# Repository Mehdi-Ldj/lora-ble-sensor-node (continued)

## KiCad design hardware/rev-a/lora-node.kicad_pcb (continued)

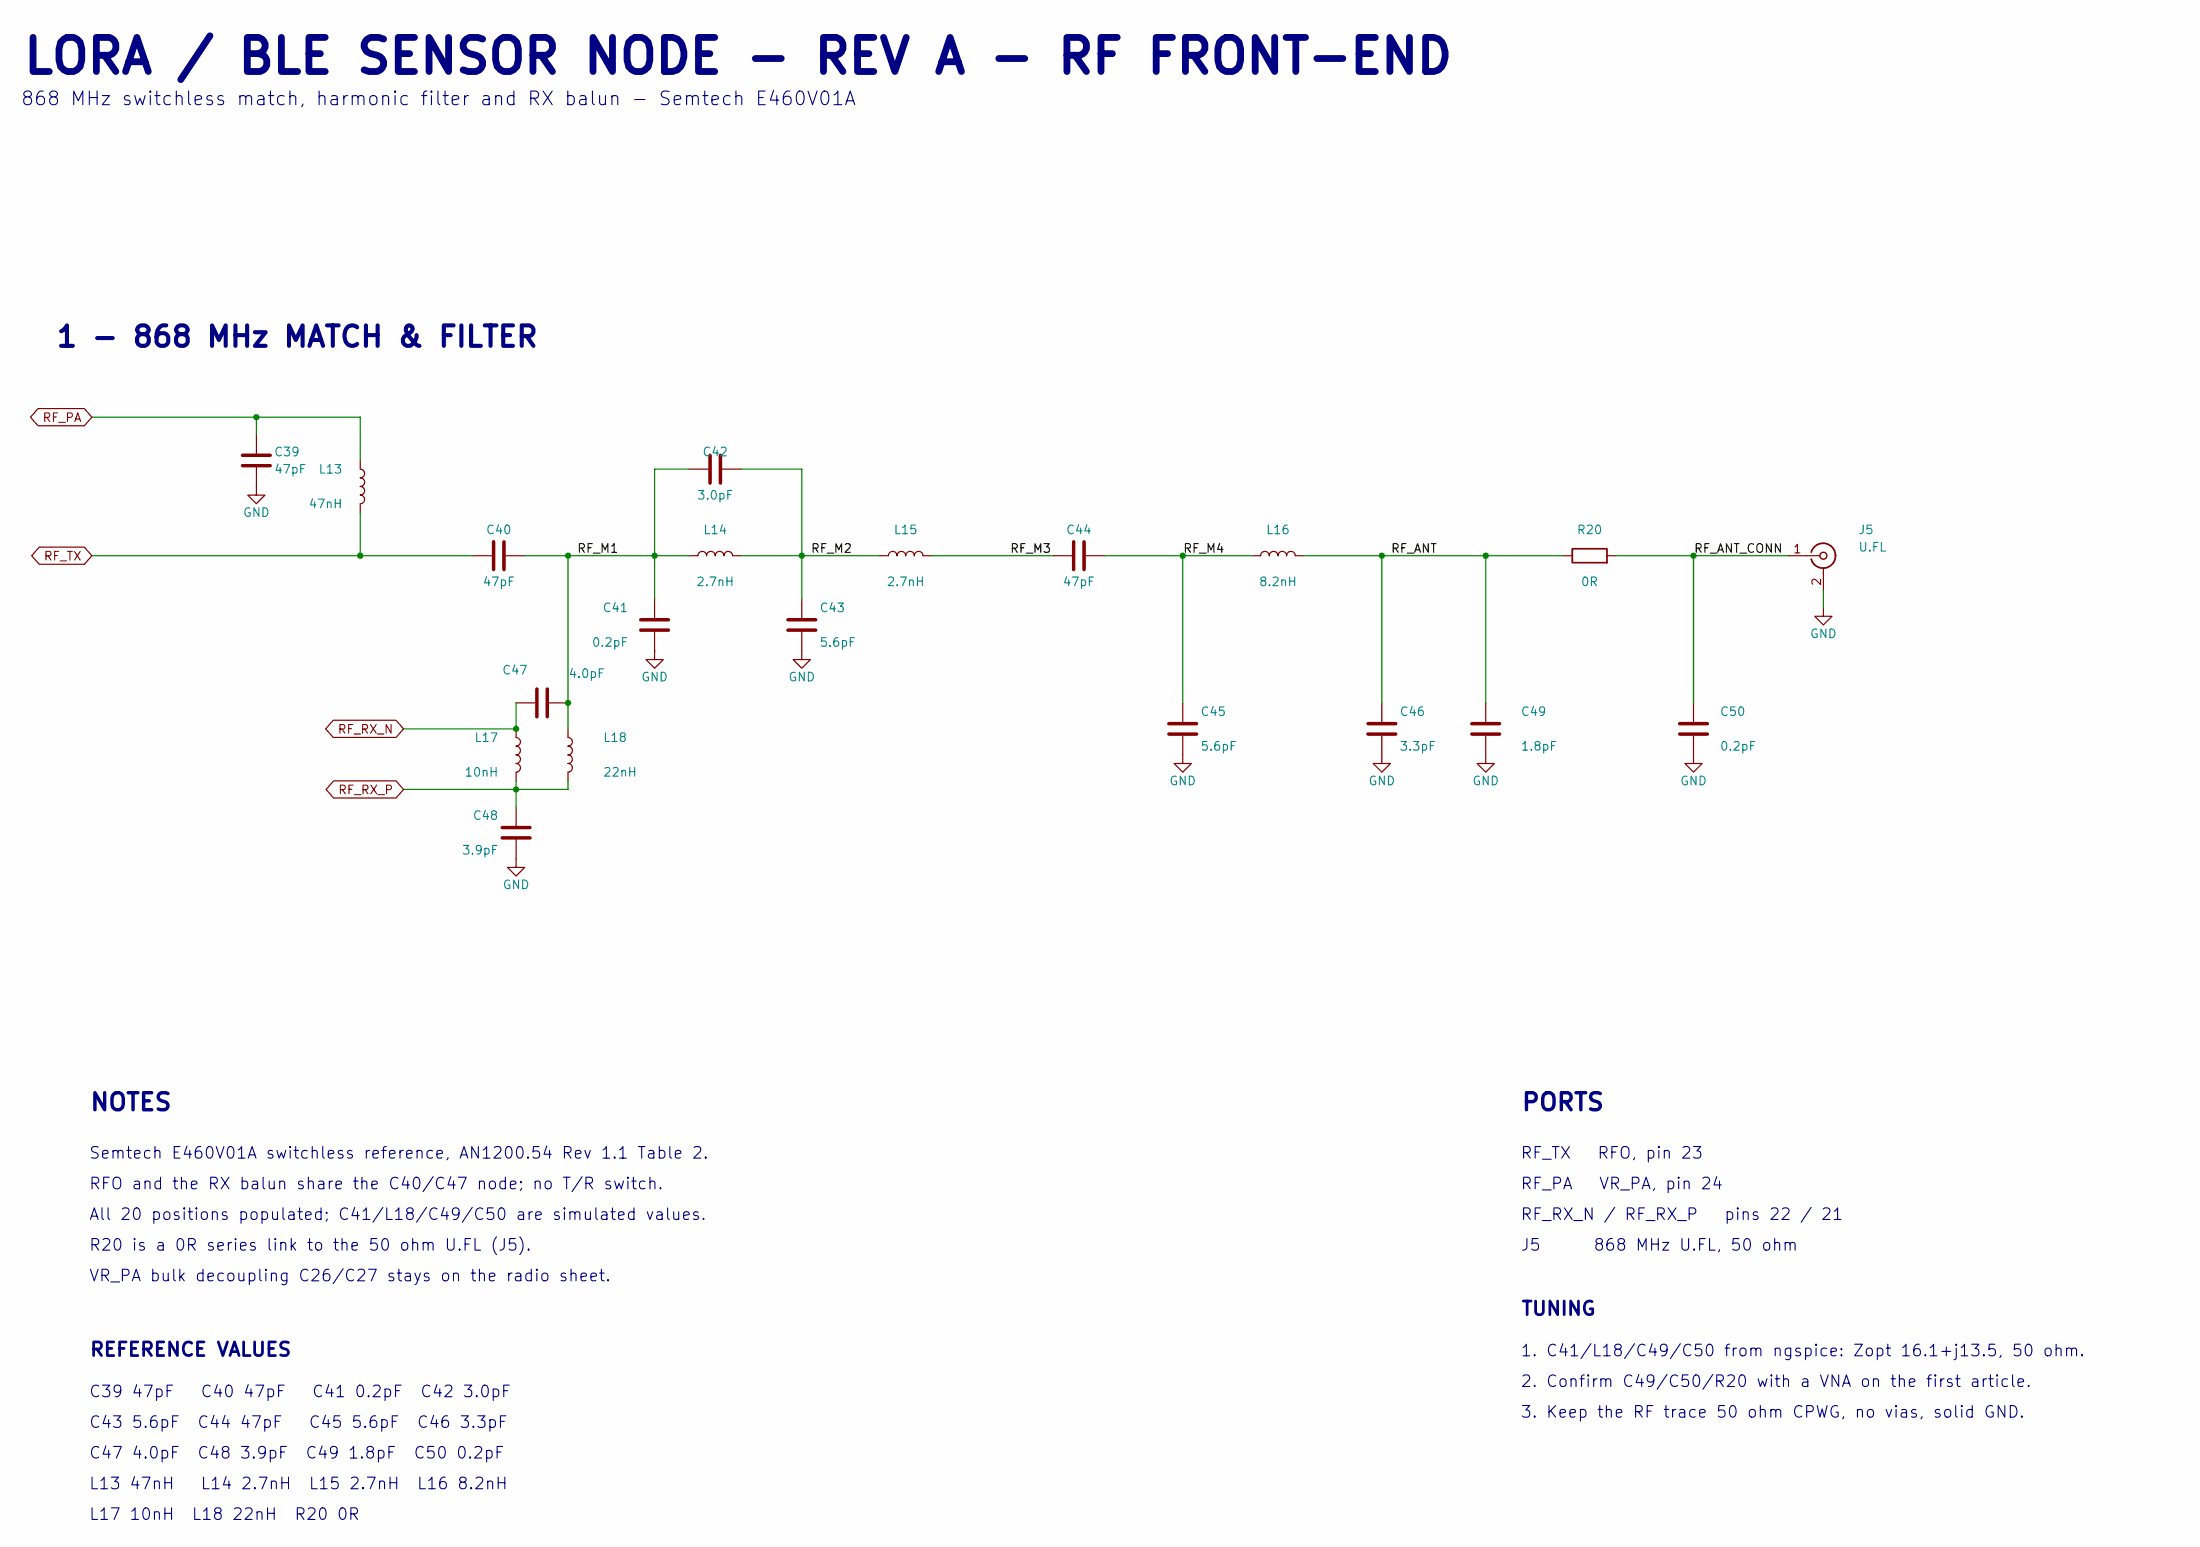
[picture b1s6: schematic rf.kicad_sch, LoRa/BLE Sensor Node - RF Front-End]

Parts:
C39, C40, C44: 47pF; C_0402_1005Metric; MPN CC0402JRNPO9BN470; LCSC C60137
C41, C50: 0.2pF; C_0402_1005Metric; MPN CQ0402BRNPO9BNR20; LCSC C1855077
C42: 3.0pF; C_0402_1005Metric; MPN CC0402BRNPO9BN3R0; LCSC C327228
C43, C45: 5.6pF; C_0402_1005Metric; MPN CC0402BRNPO9BN5R6; LCSC C505468
C46: 3.3pF; C_0402_1005Metric; MPN CC0402BRNPO9BN3R3; LCSC C327287
C47: 4.0pF; C_0402_1005Metric; MPN CC0402BRNPO9BN4R0; LCSC C541337
C48: 3.9pF; C_0402_1005Metric; MPN CC0402BRNPO9BN3R9; LCSC C505474
C49: 1.8pF; C_0402_1005Metric; MPN CC0402BRNPO9BN1R8; LCSC C327209
J5: U.FL; U.FL_Hirose_U.FL-R-SMT-1_Vertical; MPN U.FL-R-SMT-1(80); LCSC C88374
L13: 47nH; L_0402_1005Metric; MPN LQW15AN47NG00D; LCSC C22334
L14, L15: 2.7nH; L_0402_1005Metric; MPN LQW15AN2N7C00D; LCSC C98058
L16: 8.2nH; L_0402_1005Metric; MPN LQW15AN8N2G00D; LCSC C84404
L17: 10nH; L_0402_1005Metric; MPN LQW15AN10NG00D; LCSC C90642
L18: 22nH; L_0402_1005Metric; MPN LQW15AN22NG00D; LCSC C86129
R20: 0R; R_0402_1005Metric; MPN 0402WGF0000TCE; LCSC C17168

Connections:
/RF/RF_ANT: C46.1, C49.1, L16.2, R20.1
/RF/RF_ANT_CONN: C50.1, J5.1 (In), R20.2
/RF/RF_M1: C40.2, C41.1, C42.1, C47.1, L14.1, L18.1
/RF/RF_M2: C42.2, C43.1, L14.2, L15.1
/RF/RF_M3: C44.1, L15.2
/RF/RF_M4: C44.2, C45.1, L16.1
GND: C39.2, C41.2, C43.2, C45.2, C46.2, C48.2, C49.2, C50.2, J5.2 (Ext); also elsewhere on the board
RF_PA: C39.1, L13.1; also elsewhere on the board
RF_RX_N: C47.2, L17.1; also elsewhere on the board
RF_RX_P: C48.1, L17.2, L18.2; also elsewhere on the board
RF_TX: C40.1, L13.2; also elsewhere on the board

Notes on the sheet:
REFERENCE VALUES
RF_PA VR_PA, pin 24
J5 868 MHz U.FL, 50 ohm
1. C41/L18/C49/C50 from ngspice: Zopt 16.1+j13.5, 50 ohm.
RFO and the RX balun share the C40/C47 node; no T/R switch.
2. Confirm C49/C50/R20 with a VNA on the first article.
PORTS
TUNING
LORA / BLE SENSOR NODE - REV A - RF FRONT-END
L17 10nH L18 22nH R20 0R
All 20 positions populated; C41/L18/C49/C50 are simulated values.
RF_RX_N / RF_RX_P pins 22 / 21
C39 47pF C40 47pF C41 0.2pF C42 3.0pF
868 MHz switchless match, harmonic filter and RX balun - Semtech E460V01A
R20 is a 0R series link to the 50 ohm U.FL (J5).
3. Keep the RF trace 50 ohm CPWG, no vias, solid GND.
RF_TX RFO, pin 23
1 - 868 MHz MATCH & FILTER
C43 5.6pF C44 47pF C45 5.6pF C46 3.3pF
L13 47nH L14 2.7nH L15 2.7nH L16 8.2nH
VR_PA bulk decoupling C26/C27 stays on the radio sheet.
Semtech E460V01A switchless reference, AN1200.54 Rev 1.1 Table 2.
NOTES
C47 4.0pF C48 3.9pF C49 1.8pF C50 0.2pF

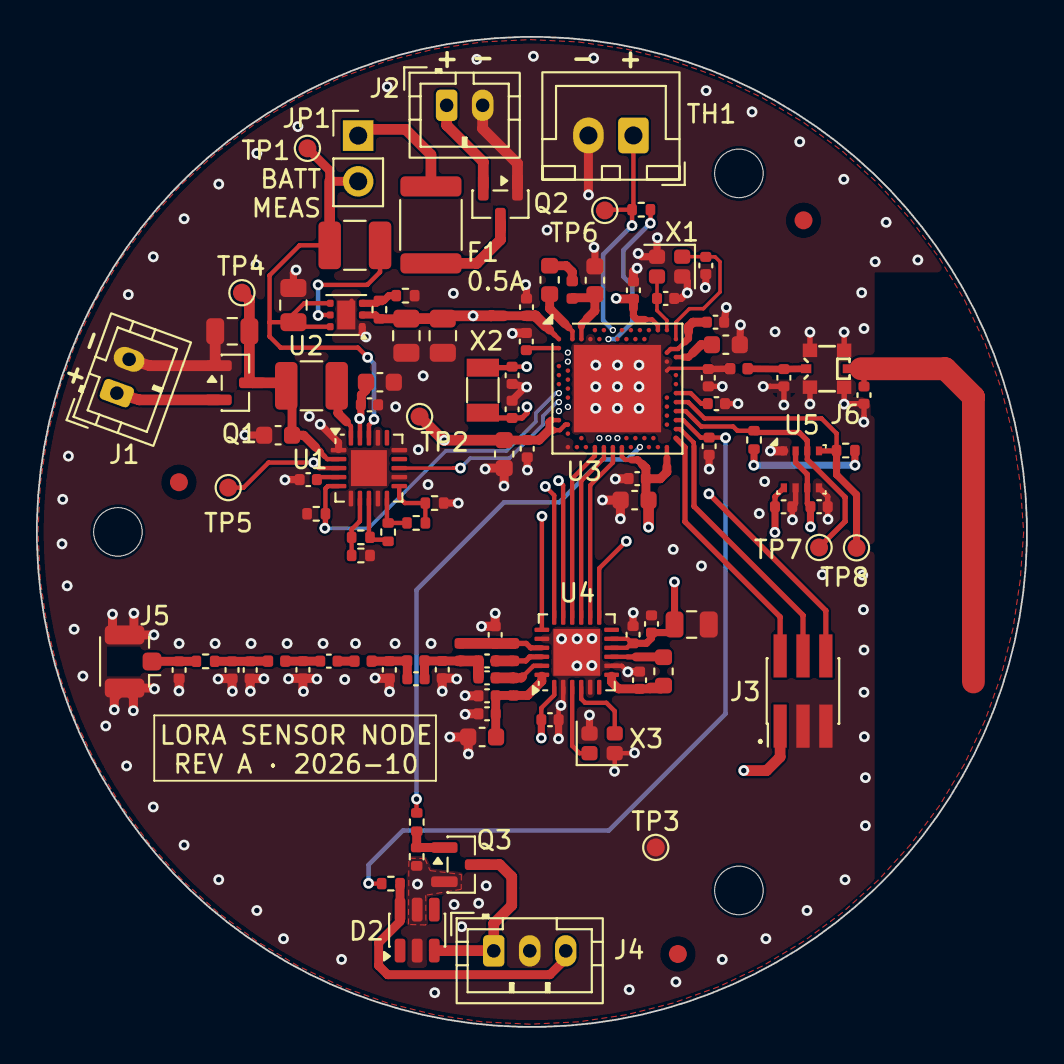
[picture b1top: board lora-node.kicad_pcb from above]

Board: 4 copper layers, 55.0 x 55.0 mm, 110 parts (0 on the bottom side), 66 nets.

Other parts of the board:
FID1, FID2, FID3: Fiducial; Fiducial_1mm_Mask2mm
H1, H2, H3: M2.5; MountingHole_2.7mm_M2.5_DIN965
